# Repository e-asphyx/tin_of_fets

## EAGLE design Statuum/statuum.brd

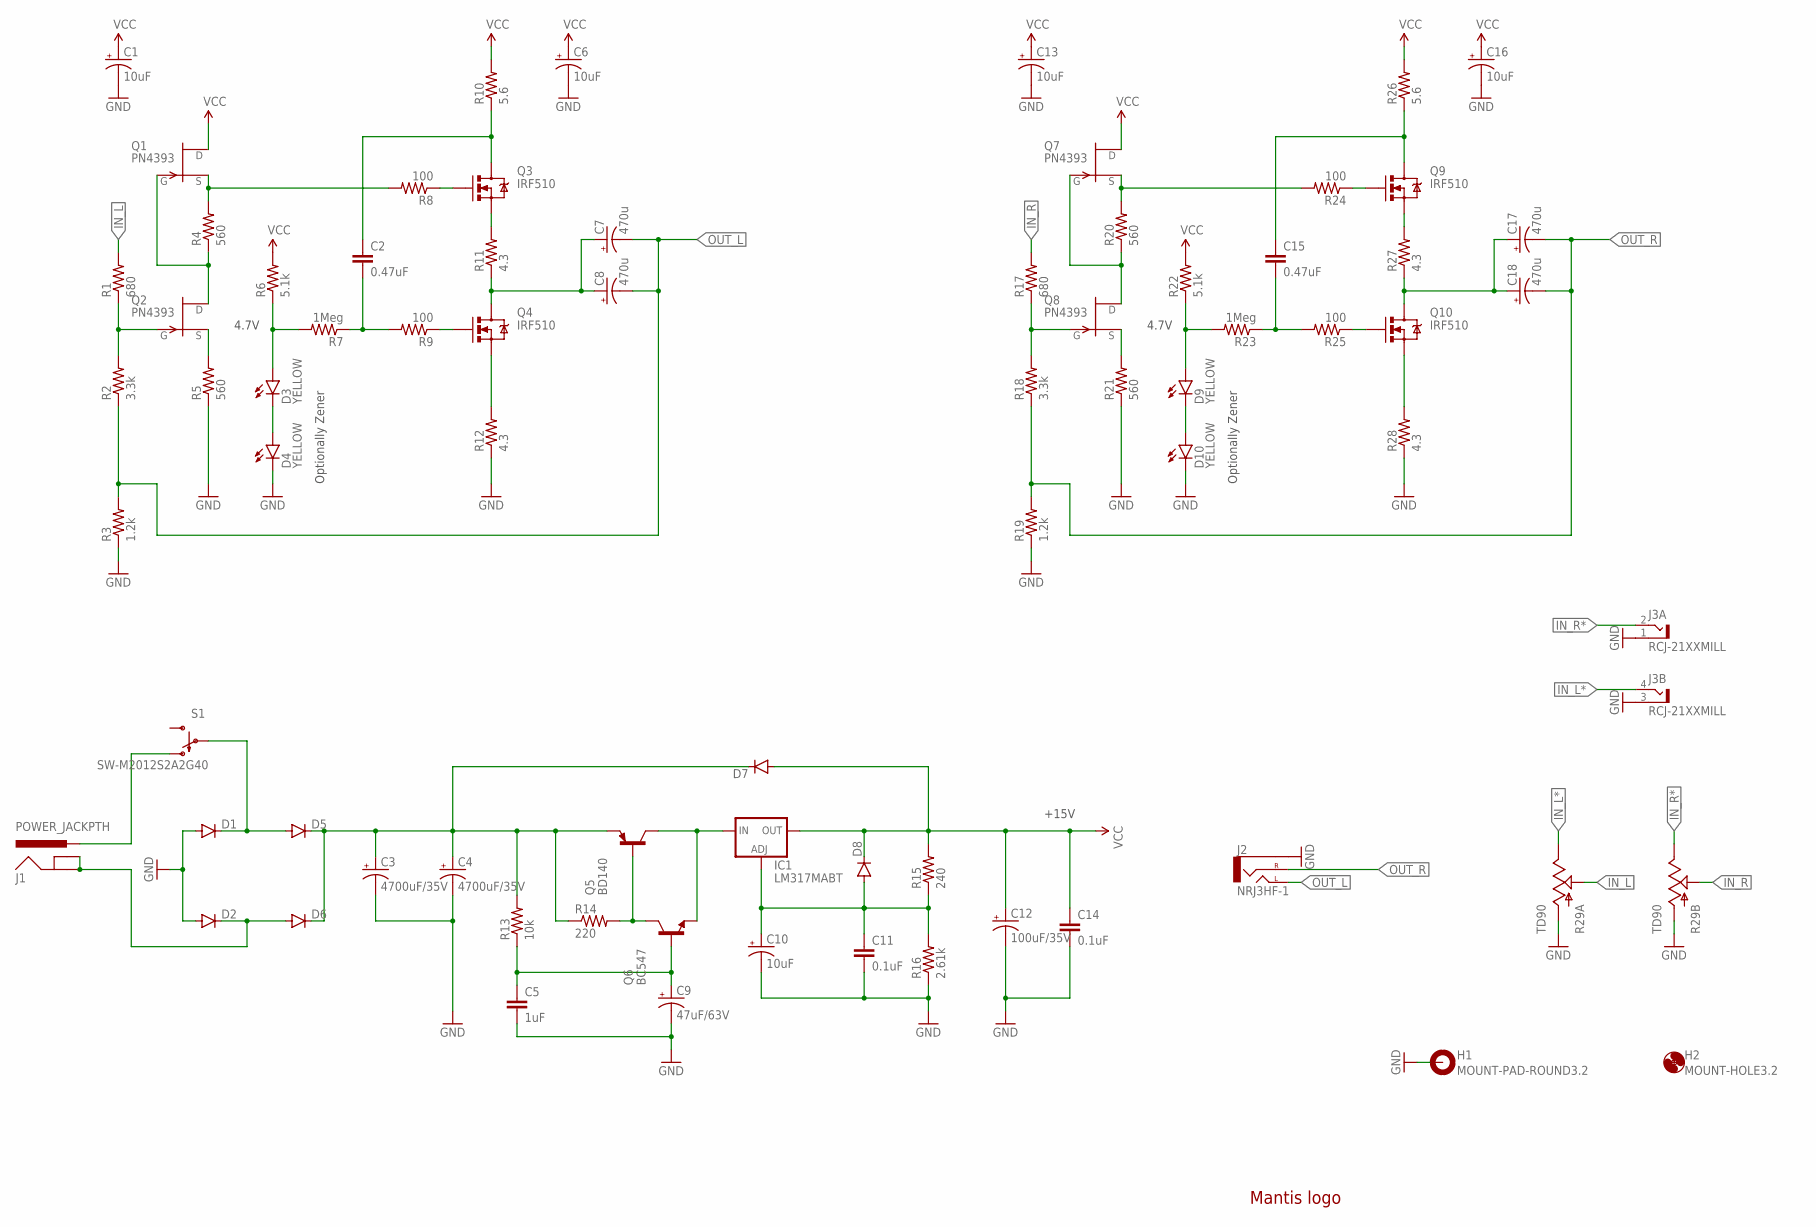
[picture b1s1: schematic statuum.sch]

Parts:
C1, C6, C10, C13, C16: 10uF; CPOL-RADIAL-5/2.5-SM
C2, C15: 0.47uF; C5B3.5
C3, C4: 4700uF/35V; CPOL-RADIAL-16/7.5
C5: 1uF; CAP-PTH-SMALL
C7, C8, C17, C18: 470u; CPOL-RADIAL-8/3.5
C9: 47uF/63V; CPOL-RADIAL-6.5/2.5
C11, C14: 0.1uF; CAP-PTH-SMALL
C12: 100uF/35V; CPOL-RADIAL-8/3.5
D1, D2, D5, D6, D7, D8: DIODEPTH; DIODE-1N4001
D3, D4, D9, D10: YELLOW; LED3MM-SM
H1: MOUNT-PAD-ROUND3.2; 3,2-PAD
H2: MOUNT-HOLE3.2; 3,2
IC1: LM317MABT; TO220L1
J1: POWER_JACKPTH; POWER_JACK_PTH
J2: NRJ3HF-1; NRJ3HF
J3: RCJ-21XXMILL; RCJ-21-MILL
LOGO1: LOGO-MANTIS
Q1, Q2, Q7, Q8: PN4393; TO-92
Q3, Q4, Q9, Q10: IRF510; TO220-HORIZ
Q5: BD140; TO126
Q6: BC547; TO-92
R1, R17: 680; AXIAL-0.4
R2, R18: 3.3k; AXIAL-0.4
R3, R19: 1.2k; AXIAL-0.4
R4, R5, R20, R21: 560; AXIAL-0.4
R6, R22: 5.1k; AXIAL-0.4
R7, R23: 1Meg; AXIAL-0.4
R8, R9, R24, R25: 100; AXIAL-0.4
R10, R26: 5.6; AXIAL-0.4
R11, R12, R27, R28: 4.3; AXIAL-0.4
R13: 10k; AXIAL-0.4
R14: 220; AXIAL-0.4
R15: 240; AXIAL-0.4
R16: 2.61k; AXIAL-0.4
R29: TD90; PTD902
S1: SW-M2012S2A2G40

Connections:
GND: C1.2 (-), C3.2 (-), C4.2 (-), C5.2, C6.2 (-), C9.2 (-), C10.2 (-), C11.2, C12.2 (-), C13.2 (-), C14.2, C16.2 (-), D1.A, D2.A, D4.K (C), D10.K (C), H1.B3,2, J2.S (SLEEVE), J3.1 (S), J3.3 (S), R3.P$1 (1), R5.P$1 (1), R12.P$1 (1), R16.P$1 (1), R19.P$1 (1), R21.P$1 (1), R28.P$1 (1), R29.R1.1 (A), R29.R2.1 (A)
IN_L: R1.P$2 (2), R29.R1.2 (S)
IN_L*: J3.4 (T), R29.R1.3 (E)
IN_R: R17.P$2 (2), R29.R2.2 (S)
IN_R*: J3.2 (T), R29.R2.3 (E)
unnamed: Q1.2 (S), R4.P$2 (2), R8.P$2 (2)
unnamed: Q1.3 (G), Q2.1 (D), R4.P$1 (1)
unnamed: Q2.2 (S), R5.P$2 (2)
unnamed: D3.K (C), D4.A
unnamed: Q3.1 (G), R8.P$1 (1)
unnamed: Q2.3 (G), R1.P$1 (1), R2.P$2 (2)
unnamed: Q3.3 (S), R11.P$2 (2)
unnamed: Q4.1 (G), R9.P$1 (1)
unnamed: Q9.3 (S), R27.P$2 (2)
unnamed: Q4.3 (S), R12.P$2 (2)
unnamed: C2.1, Q3.2 (D), R10.P$1 (1)
unnamed: C7.1 (+), C8.1 (+), Q4.2 (D), R11.P$1 (1)
unnamed: D1.C, D5.A, S1.S
unnamed: D3.A, R6.P$1 (1), R7.P$2 (2)
unnamed: C2.2, R7.P$1 (1), R9.P$2 (2)
unnamed: Q7.2 (S), R20.P$2 (2), R24.P$2 (2)
unnamed: Q7.3 (G), Q8.1 (D), R20.P$1 (1)
unnamed: Q8.2 (S), R21.P$2 (2)
unnamed: Q8.3 (G), R17.P$1 (1), R18.P$2 (2)
unnamed: Q9.1 (G), R24.P$1 (1)
unnamed: Q10.1 (G), R25.P$1 (1)
unnamed: Q10.3 (S), R28.P$2 (2)
unnamed: C15.1, Q9.2 (D), R26.P$1 (1)
unnamed: D9.A, R22.P$1 (1), R23.P$2 (2)
unnamed: D9.K (C), D10.A
unnamed: Q5.3 (B), Q6.1 (C), R14.P$2 (2)
unnamed: C5.1, C9.1 (+), Q6.2 (B), R13.P$1 (1)
unnamed: C15.2, R23.P$1 (1), R25.P$2 (2)
unnamed: C17.1 (+), C18.1 (+), Q10.2 (D), R27.P$1 (1)
unnamed: D2.C, D6.A, J1.GND, J1.GNDBREAK
unnamed: C10.1 (+), C11.1, D8.A, IC1.1 (ADJ), R15.P$1 (1), R16.P$2 (2)
unnamed: C3.1 (+), C4.1 (+), D5.C, D6.C, D7.C, Q5.1 (E), R13.P$2 (2), R14.P$1 (1)
unnamed: J1.PWR, S1.UP-CONNECT (O)
unnamed: IC1.3 (IN), Q5.2 (C), Q6.3 (E)
OUT_L: C7.2 (-), C8.2 (-), J2.T (LEFT), R2.P$1 (1), R3.P$2 (2)
OUT_R: C17.2 (-), C18.2 (-), J2.R (RIGHT), R18.P$1 (1), R19.P$2 (2)
VCC: C1.1 (+), C6.1 (+), C12.1 (+), C13.1 (+), C14.1, C16.1 (+), D7.A, D8.C, IC1.2 (OUT), Q1.1 (D), Q7.1 (D), R6.P$2 (2), R10.P$2 (2), R15.P$2 (2), R22.P$2 (2), R26.P$2 (2)

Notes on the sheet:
Optionally Zener
+15V
4.7V

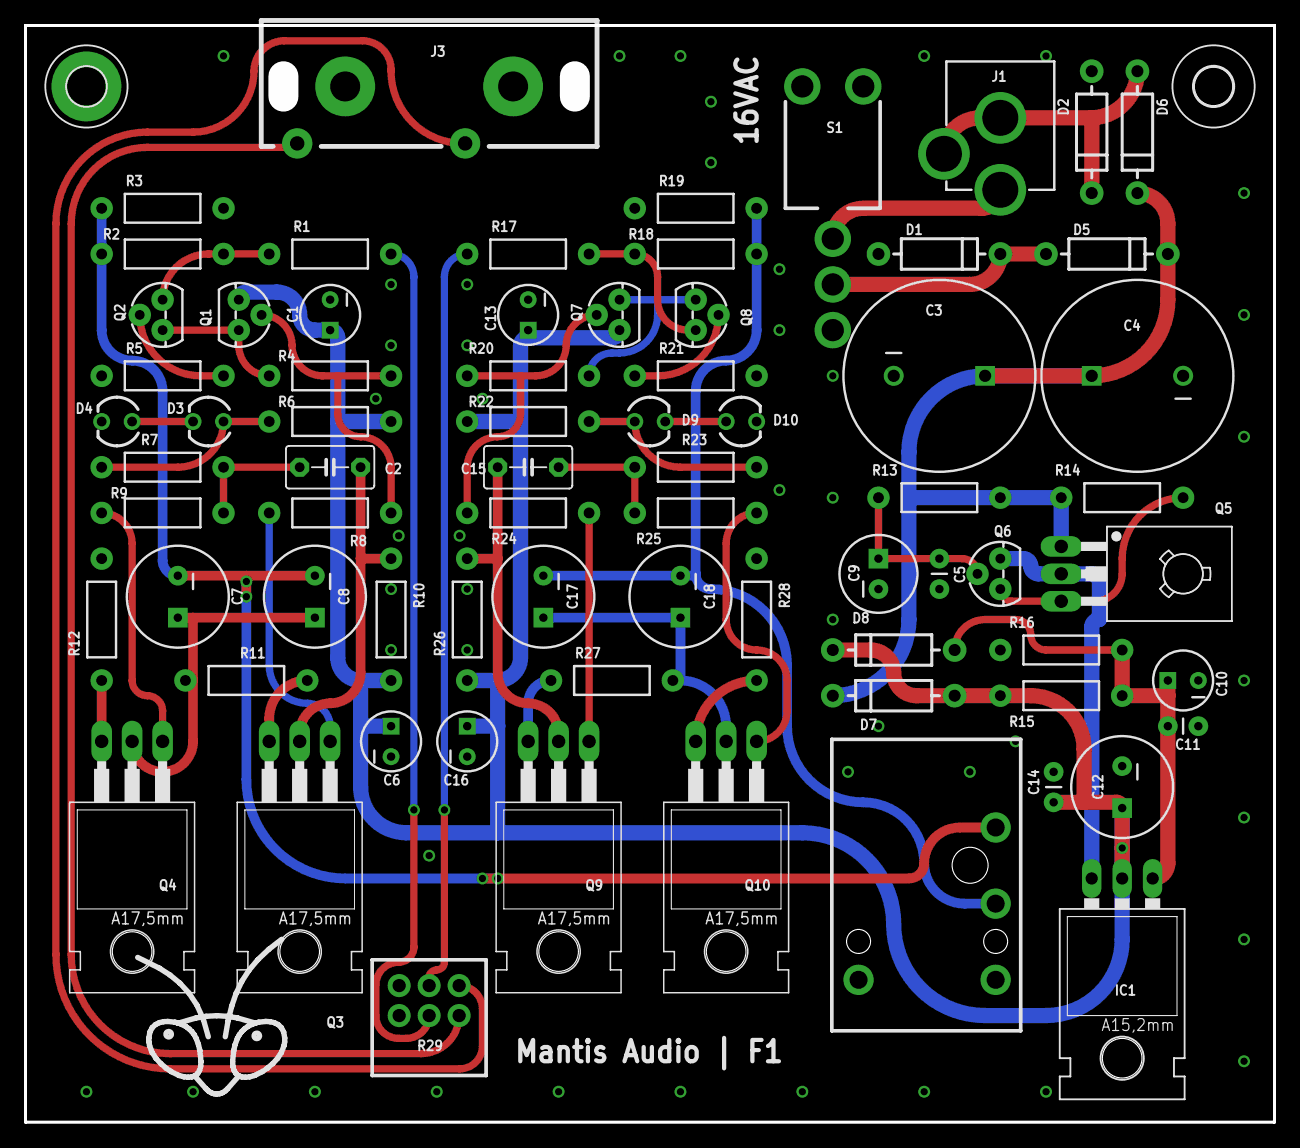
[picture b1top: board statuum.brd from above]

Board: 2 copper layers, 101.9 x 89.2 mm, 75 parts (0 on the bottom side), 42 nets.

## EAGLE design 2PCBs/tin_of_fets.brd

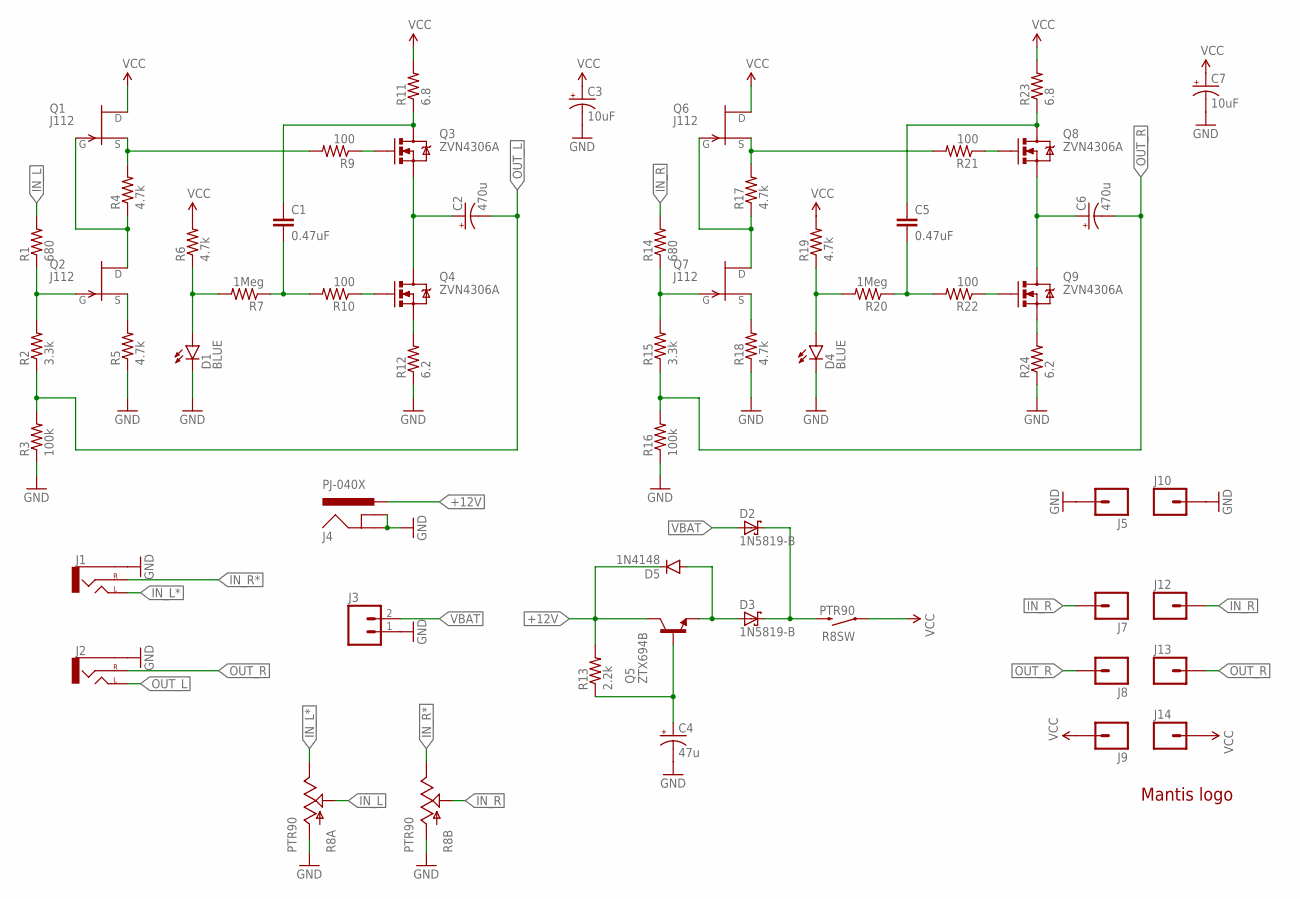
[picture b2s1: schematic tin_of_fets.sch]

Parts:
C1, C5: 0.47uF; C5B3.5
C2, C6: 470u; CPOL-RADIAL-8/3.5
C3, C7: 10uF; CPOL-RADIAL-10UF-25V-SM
C4: 47u; CPOL-RADIAL-10UF-25V-SM
D1, D4: BLUE; LED3MM-SM
D2, D3: 1N5819-B; DO41-7.6
D5: 1N4148; DIODE-1N4148
J1, J2: AUDIO-JACKPTH; AUDIO-JACK
J3: M02PTH; 1X02
J4: PJ-040X
J5, J7, J8, J9, J10, J12, J13, J14: M01PTH; 1X01
LOGO1: LOGO-MANTIS
Q1, Q2, Q6, Q7: J112; TO-92
Q3, Q4, Q8, Q9: ZVN4306A; TO-92
Q5: ZTX694B; TO-92
R1, R14: 680; AXIAL-0.4-SM
R2, R15: 3.3k; AXIAL-0.4-SM
R3, R16: 100k; AXIAL-0.4-SM
R4, R5, R6, R17, R18, R19: 4.7k; AXIAL-0.4-SM
R7, R20: 1Meg; AXIAL-0.4-SM
R8: PTR90; PTR902
R9, R10, R21, R22: 100; AXIAL-0.4-SM
R11, R23: 6.8; AXIAL-0.4-SM
R12, R24: 6.2; AXIAL-0.4-SM
R13: 2.2k; AXIAL-0.4-SM

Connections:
+12V: D5.C, J4.1 (PWR), Q5.3 (C), R13.P$2 (2)
GND: C3.2 (-), C4.2 (-), C7.2 (-), D1.K (C), D4.K (C), J1.SLEEVE, J2.SLEEVE, J3.1, J4.2 (GND), J4.3 (GNDBREAK), J5.1, J10.1, R3.P$1 (1), R5.P$1 (1), R8.R1.1 (A), R8.R2.1 (A), R12.P$1 (1), R16.P$1 (1), R18.P$1 (1), R24.P$1 (1)
IN_L: R1.P$2 (2), R8.R1.2 (S)
IN_L*: J1.TIP (LEFT), R8.R1.3 (E)
IN_R: J7.1, J12.1, R8.R2.2 (S), R14.P$2 (2)
IN_R*: J1.RING (RIGHT), R8.R2.3 (E)
unnamed: Q1.2 (S), R4.P$2 (2), R9.P$2 (2)
unnamed: Q1.3 (G), Q2.1 (D), R4.P$1 (1)
unnamed: Q2.2 (S), R5.P$2 (2)
unnamed: Q6.2 (S), R17.P$2 (2), R21.P$2 (2)
unnamed: Q3.2 (G), R9.P$1 (1)
unnamed: Q2.3 (G), R1.P$1 (1), R2.P$2 (2)
unnamed: Q6.3 (G), Q7.1 (D), R17.P$1 (1)
unnamed: Q4.2 (G), R10.P$1 (1)
unnamed: Q4.1 (S), R12.P$2 (2)
unnamed: C1.1, Q3.3 (D), R11.P$1 (1)
unnamed: Q7.2 (S), R18.P$2 (2)
unnamed: C1.2, R7.P$1 (1), R10.P$2 (2)
unnamed: D1.A, R6.P$1 (1), R7.P$2 (2)
unnamed: Q7.3 (G), R14.P$1 (1), R15.P$2 (2)
unnamed: Q8.2 (G), R21.P$1 (1)
unnamed: Q9.2 (G), R22.P$1 (1)
unnamed: Q9.1 (S), R24.P$2 (2)
unnamed: C5.1, Q8.3 (D), R23.P$1 (1)
unnamed: C5.2, R20.P$1 (1), R22.P$2 (2)
unnamed: D4.A, R19.P$1 (1), R20.P$2 (2)
unnamed: D3.A, D5.A, Q5.1 (E)
unnamed: C4.1 (+), Q5.2 (B), R13.P$1 (1)
OUT_L: C2.2 (-), J2.TIP (LEFT), R2.P$1 (1), R3.P$2 (2)
OUT_L*: C2.1 (+), Q3.1 (S), Q4.3 (D)
OUT_R: C6.2 (-), J2.RING (RIGHT), J8.1, J13.1, R15.P$1 (1), R16.P$2 (2)
OUT_R*: C6.1 (+), Q8.1 (S), Q9.3 (D)
VBAT: D2.A, J3.2
VCC: C3.1 (+), C7.1 (+), J9.1, J14.1, Q1.1 (D), Q6.1 (D), R6.P$2 (2), R8.SW1 (1), R11.P$2 (2), R19.P$2 (2), R23.P$2 (2)
VCC*: D2.C, D3.C, R8.SW2 (2)

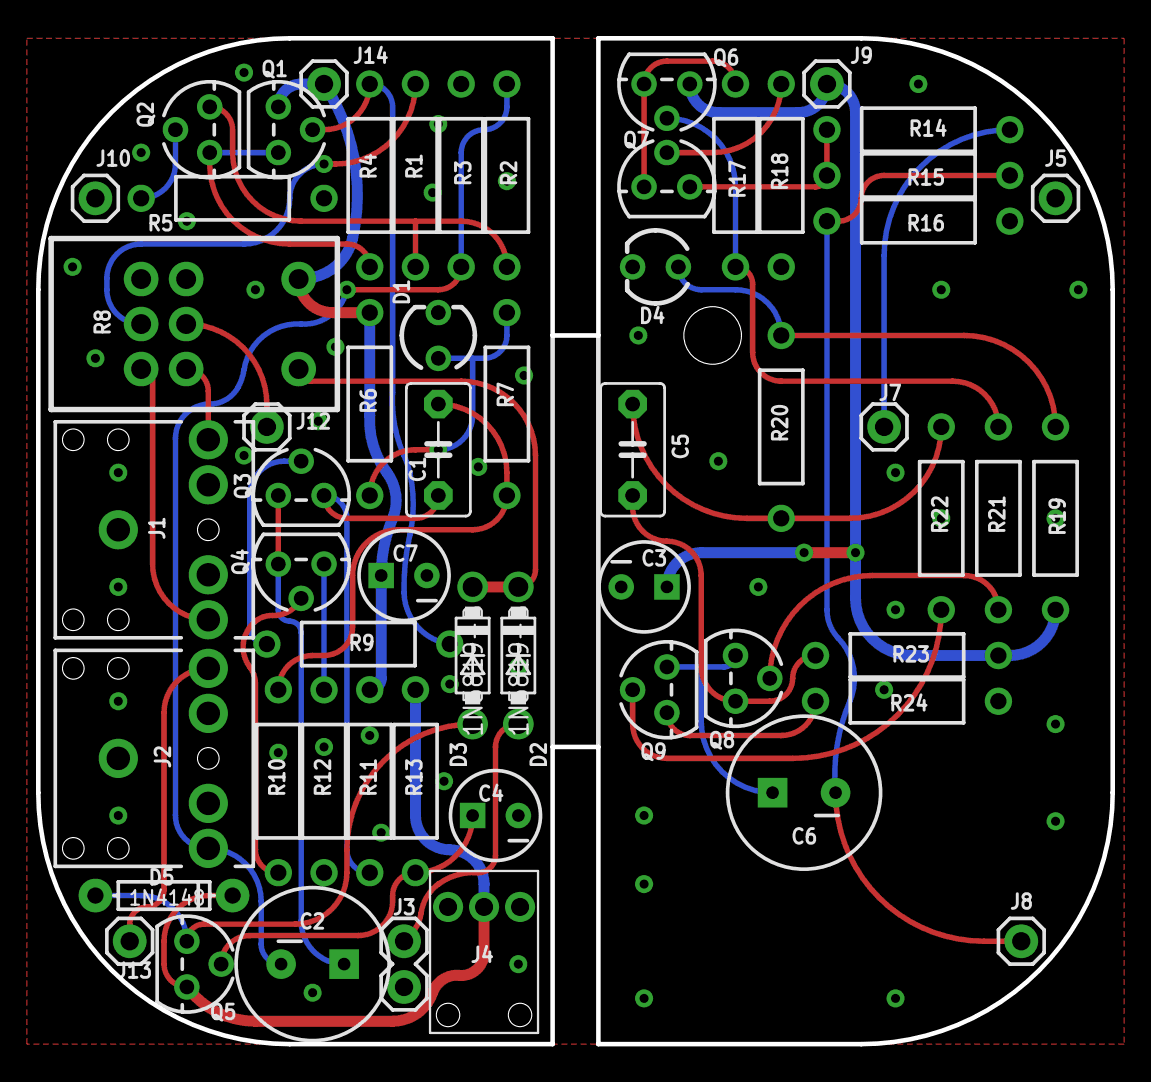
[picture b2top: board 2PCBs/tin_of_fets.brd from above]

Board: 2 copper layers, 59.7 x 55.9 mm, 58 parts (1 on the bottom side), 35 nets.

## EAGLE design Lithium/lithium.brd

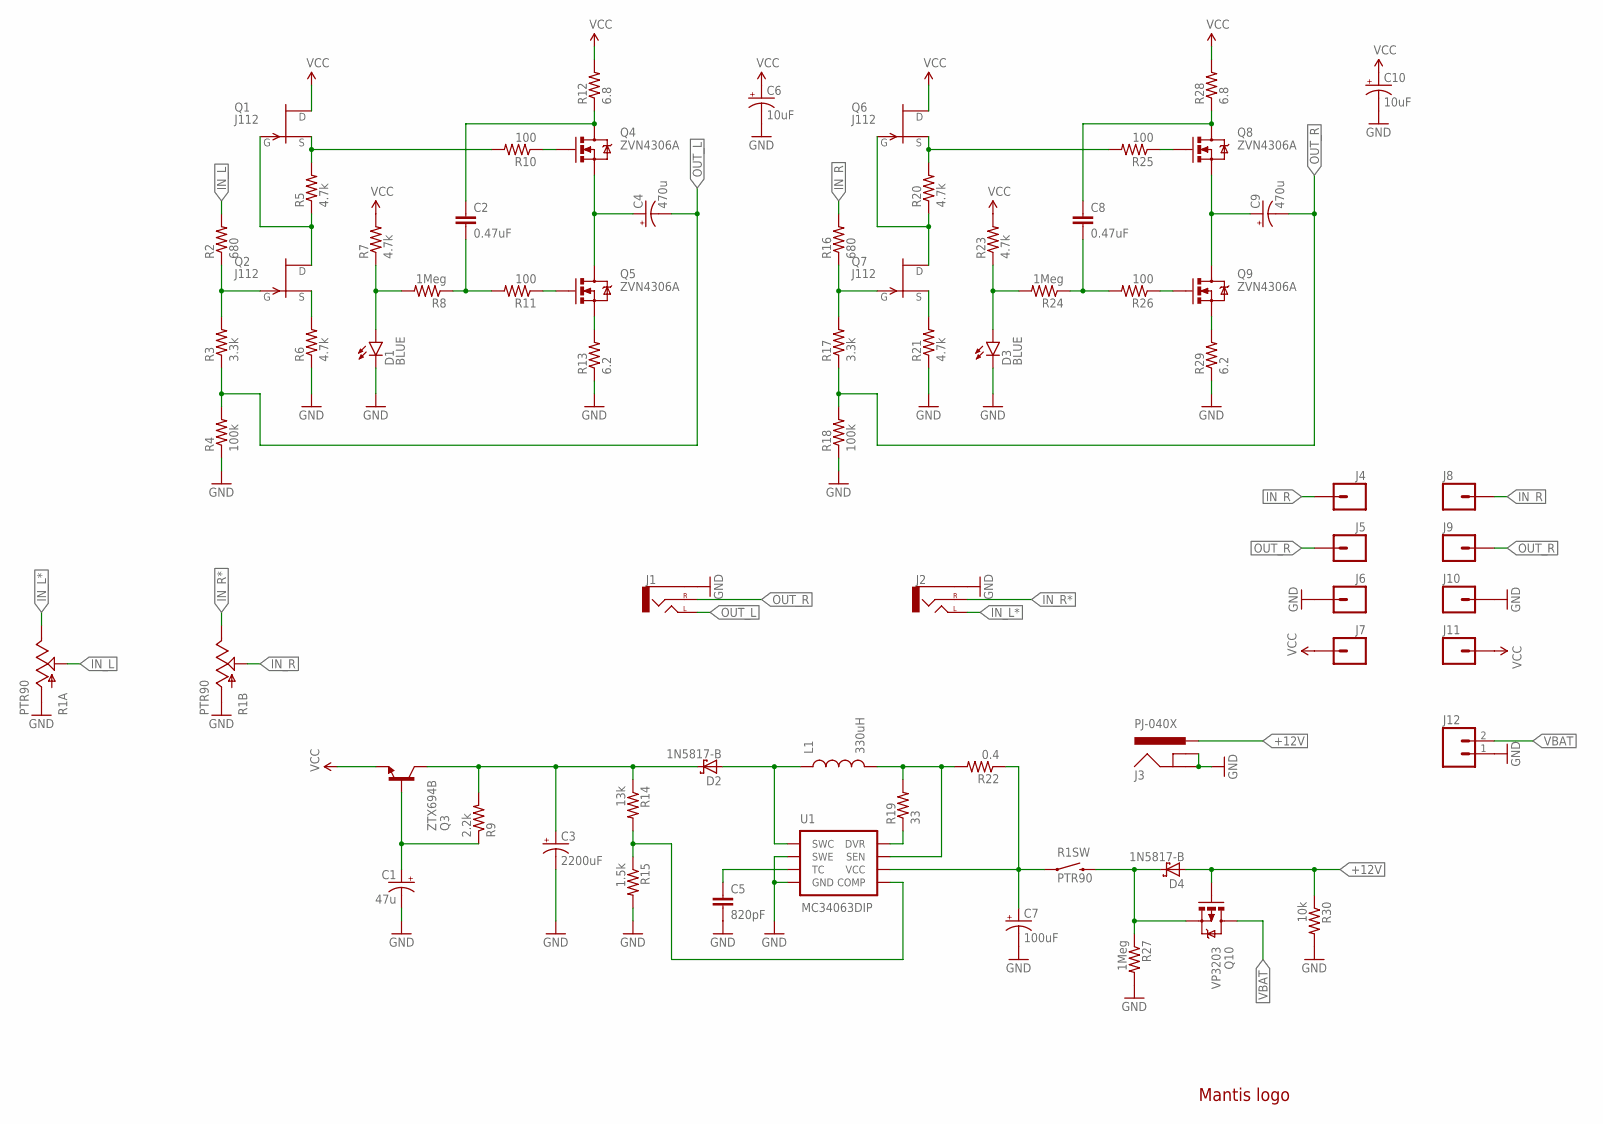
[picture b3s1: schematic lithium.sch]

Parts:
C1: 47u; CPOL-RADIAL-10UF-25V-SM
C2, C8: 0.47uF; C5B3.5
C3: 2200uF; CPOL-RADIAL-1000UF-25V
C4, C9: 470u; CPOL-RADIAL-8/3.5
C5: 820pF; CAP-PTH-SMALL
C6, C10: 10uF; CPOL-RADIAL-10UF-25V-SM
C7: 100uF; CPOL-RADIAL-100UF-25V
D1, D3: BLUE; LED3MM-SM
D2, D4: 1N5817-B; DO41-7.6
J1, J2: AUDIO-JACKPTH; AUDIO-JACK
J3: PJ-040X
J4, J5, J6, J7, J8, J9, J10, J11: M01PTH; 1X01
J12: M02PTH; 1X02
L1: 330uH; RLB0912
LOGO1: LOGO-MANTIS
Q1, Q2, Q6, Q7: J112; TO-92
Q3: ZTX694B; TO-92
Q4, Q5, Q8, Q9: ZVN4306A; TO-92
Q10: VP3203; TO-92
R1: PTR90; PTR902
R2, R16: 680; AXIAL-0.4-SM
R3, R17: 3.3k; AXIAL-0.4-SM
R4, R18: 100k; AXIAL-0.4-SM
R5, R6, R7, R20, R21, R23: 4.7k; AXIAL-0.4-SM
R8, R24, R27: 1Meg; AXIAL-0.4-SM
R9: 2.2k; AXIAL-0.4-SM
R10, R11, R25, R26: 100; AXIAL-0.4-SM
R12, R28: 6.8; AXIAL-0.4-SM
R13, R29: 6.2; AXIAL-0.4-SM
R14: 13k; AXIAL-0.4-SM
R15: 1.5k; AXIAL-0.4-SM
R19: 33; AXIAL-0.4-SM
R22: 0.4; AXIAL-0.4-SM
R30: 10k; AXIAL-0.4-SM
U1: MC34063DIP; DIP-08

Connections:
+12V: D4.A, J3.1 (PWR), Q10.2 (G), R30.P$1 (1)
GND: C1.2 (-), C3.-, C5.2, C6.2 (-), C7.2 (-), C10.2 (-), D1.K (C), D3.K (C), J1.SLEEVE, J2.SLEEVE, J3.2 (GND), J3.3 (GNDBREAK), J6.1, J10.1, J12.1, R1.R1.1 (A), R1.R2.1 (A), R4.P$1 (1), R6.P$1 (1), R13.P$1 (1), R15.P$2 (2), R18.P$1 (1), R21.P$1 (1), R27.P$2 (2), R29.P$1 (1), R30.P$2 (2), U1.2 (SWE), U1.4 (GND)
IN_L: R1.R1.2 (S), R2.P$2 (2)
IN_L*: J2.TIP (LEFT), R1.R1.3 (E)
IN_R: J4.1, J8.1, R1.R2.2 (S), R16.P$2 (2)
IN_R*: J2.RING (RIGHT), R1.R2.3 (E)
unnamed: Q1.2 (S), R5.P$2 (2), R10.P$2 (2)
unnamed: Q1.3 (G), Q2.1 (D), R5.P$1 (1)
unnamed: Q2.2 (S), R6.P$2 (2)
unnamed: Q6.2 (S), R20.P$2 (2), R25.P$2 (2)
unnamed: Q4.2 (G), R10.P$1 (1)
unnamed: Q2.3 (G), R2.P$1 (1), R3.P$2 (2)
unnamed: Q6.3 (G), Q7.1 (D), R20.P$1 (1)
unnamed: Q5.2 (G), R11.P$1 (1)
unnamed: C5.1, U1.3 (TC)
unnamed: Q5.1 (S), R13.P$2 (2)
unnamed: C2.1, Q4.3 (D), R12.P$1 (1)
unnamed: Q7.2 (S), R21.P$2 (2)
unnamed: C2.2, R8.P$1 (1), R11.P$2 (2)
unnamed: D1.A, R7.P$1 (1), R8.P$2 (2)
unnamed: Q7.3 (G), R16.P$1 (1), R17.P$2 (2)
unnamed: Q8.2 (G), R25.P$1 (1)
unnamed: Q9.2 (G), R26.P$1 (1)
unnamed: R19.P$1 (1), U1.8 (DVR)
unnamed: Q9.1 (S), R29.P$2 (2)
unnamed: C8.1, Q8.3 (D), R28.P$1 (1)
unnamed: C8.2, R24.P$1 (1), R26.P$2 (2)
unnamed: D3.A, R23.P$1 (1), R24.P$2 (2)
unnamed: C7.1 (+), R1.SW1 (1), R22.P$1 (1), U1.6 (VCC)
unnamed: C1.1 (+), Q3.2 (B), R9.P$1 (1)
unnamed: D2.A, L1.1, U1.1 (SWC)
unnamed: L1.2, R19.P$2 (2), R22.P$2 (2), U1.7 (SEN)
unnamed: R14.P$2 (2), R15.P$1 (1), U1.5 (COMP)
unnamed: D4.C, Q10.1 (S), R1.SW2 (2), R27.P$1 (1)
OUT_L: C4.2 (-), J1.TIP (LEFT), R3.P$1 (1), R4.P$2 (2)
OUT_L*: C4.1 (+), Q4.1 (S), Q5.3 (D)
OUT_R: C9.2 (-), J1.RING (RIGHT), J5.1, J9.1, R17.P$1 (1), R18.P$2 (2)
OUT_R*: C9.1 (+), Q8.1 (S), Q9.3 (D)
VBAT: J12.2, Q10.3 (D)
VCC: C6.1 (+), C10.1 (+), J7.1, J11.1, Q1.1 (D), Q3.1 (E), Q6.1 (D), R7.P$2 (2), R12.P$2 (2), R23.P$2 (2), R28.P$2 (2)
VSMPS: C3.+, D2.C, Q3.3 (C), R9.P$2 (2), R14.P$1 (1)

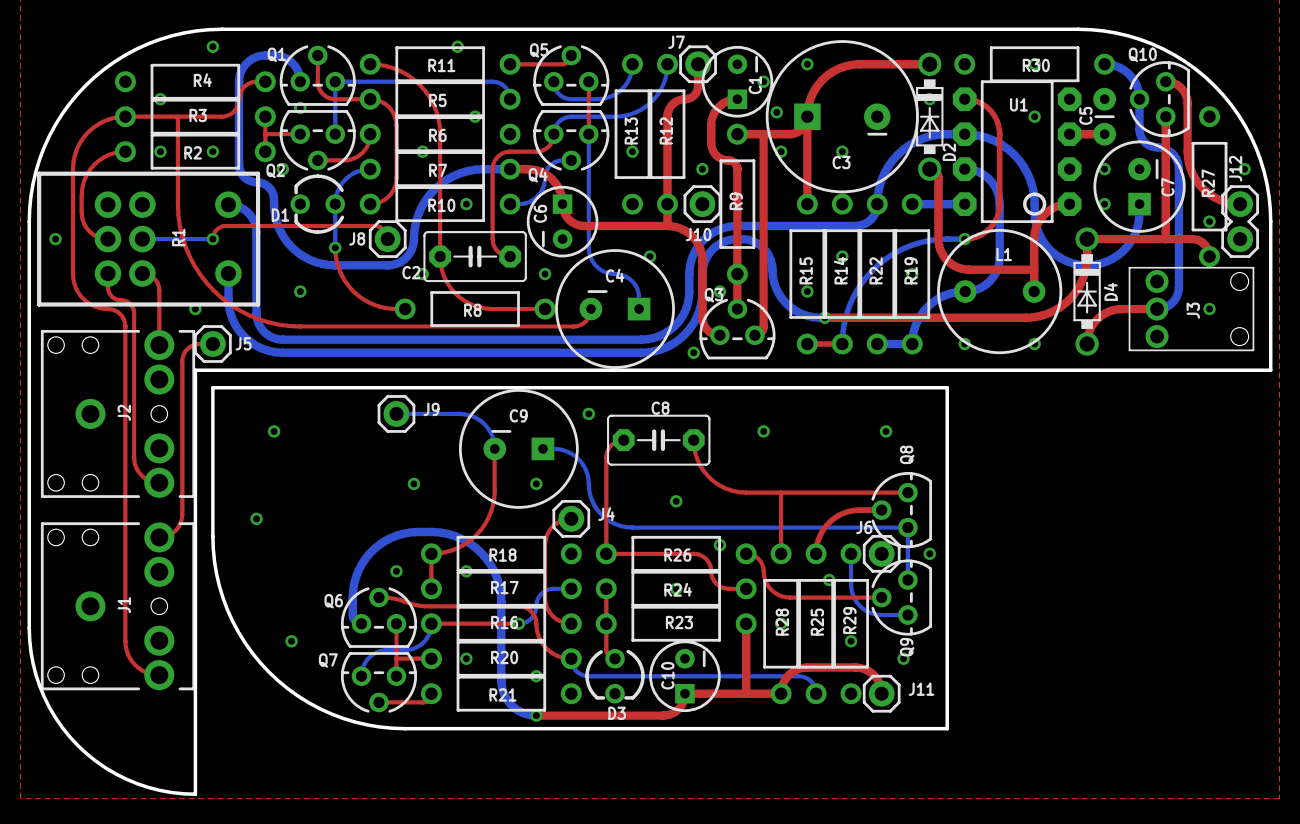
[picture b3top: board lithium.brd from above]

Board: 2 copper layers, 90.2 x 55.6 mm, 69 parts (1 on the bottom side), 41 nets.

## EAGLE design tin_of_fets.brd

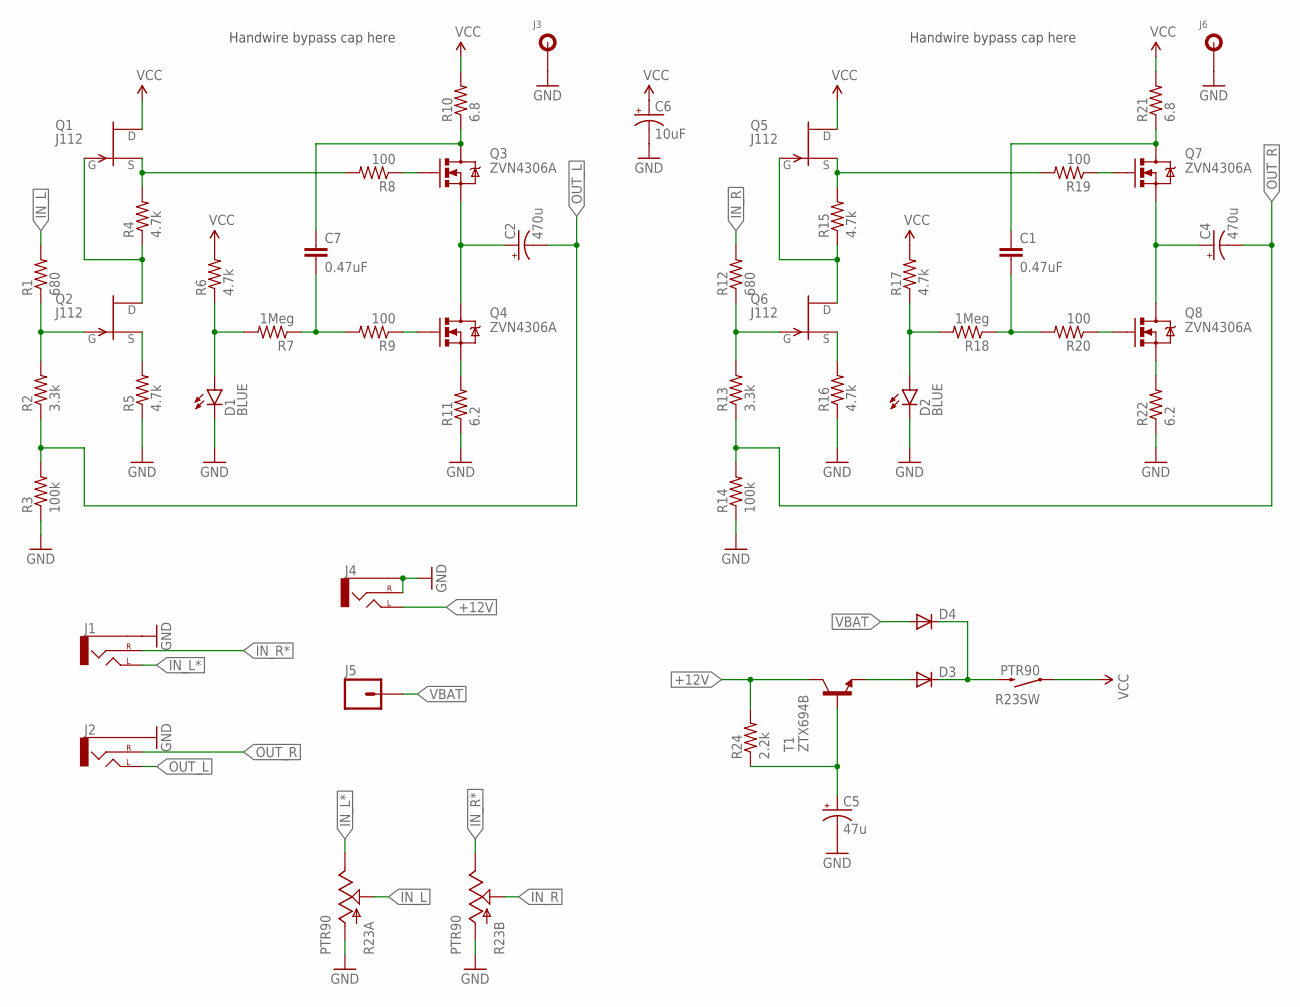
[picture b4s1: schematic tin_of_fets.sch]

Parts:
A1, A2: 9V-BATTERY-DOCU; 9V-BATTERY-DIM
A3: ALTOIDS-DOCU; ALTOIDS-INNER-DIM
C1, C7: 0.47uF; C5B3.5
C2, C4: 470u; CPOL-RADIAL-1000UF-25V
C5: 47u; CPOL-RADIAL-10UF-25V
C6: 10uF; CPOL-RADIAL-10UF-25V
D1, D2: BLUE; LED3MM
D3, D4: DIODE-C1702-05; C1702-05
J1, J2, J4: AUDIO-JACK2.5MM; STEREOJACK2.5MM_STEREOJACK2.5MM
J3, J6: PAD-NO-THERMAL
J5: M01PTH; 1X01
Q1, Q2, Q5, Q6: J112; TO92
Q3, Q4, Q7, Q8: ZVN4306A; TO-92
R1, R12: 680; AXIAL-0.1-SM
R2, R13: 3.3k; AXIAL-0.1-SM
R3, R14: 100k; AXIAL-0.1-SM
R4, R5, R6, R15, R16, R17: 4.7k; AXIAL-0.1-SM
R7, R18: 1Meg; AXIAL-0.1-SM
R8, R9, R19, R20: 100; AXIAL-0.1-SM
R10, R21: 6.8; AXIAL-0.1-SM
R11, R22: 6.2; AXIAL-0.1-SM
R23: PTR90; PTR902
R24: 2.2k; AXIAL-0.1-SM
T1: ZTX694B; TO92

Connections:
+12V: J4.TIP1 (LEFT), J4.TIP2 (LEFT), R24.P$2 (2), T1.1 (C)
GND: C5.2 (-), C6.2 (-), D1.K (C), D2.K (C), J1.SHIELD (SLEEVE), J2.SHIELD (SLEEVE), J3.P$1, J4.RING (RIGHT), J4.SHIELD (SLEEVE), J6.P$1, R3.P$1 (1), R5.P$1 (1), R11.P$1 (1), R14.P$1 (1), R16.P$1 (1), R22.P$1 (1), R23.R1.1 (A), R23.R2.1 (A)
IN_L: R1.P$2 (2), R23.R1.2 (S)
IN_L*: J1.TIP1 (LEFT), J1.TIP2 (LEFT), R23.R1.3 (E)
IN_R: R12.P$2 (2), R23.R2.2 (S)
IN_R*: J1.RING (RIGHT), R23.R2.3 (E)
unnamed: Q1.2 (S), R4.P$2 (2), R8.P$2 (2)
unnamed: Q1.1 (G), Q2.3 (D), R4.P$1 (1)
unnamed: Q2.2 (S), R5.P$2 (2)
unnamed: Q5.2 (S), R15.P$2 (2), R19.P$2 (2)
unnamed: Q3.2 (G), R8.P$1 (1)
unnamed: Q2.1 (G), R1.P$1 (1), R2.P$2 (2)
unnamed: Q5.1 (G), Q6.3 (D), R15.P$1 (1)
unnamed: Q4.2 (G), R9.P$1 (1)
unnamed: Q4.1 (S), R11.P$2 (2)
unnamed: C7.1, Q3.3 (D), R10.P$1 (1)
unnamed: Q6.2 (S), R16.P$2 (2)
unnamed: C7.2, R7.P$1 (1), R9.P$2 (2)
unnamed: D1.A, R6.P$1 (1), R7.P$2 (2)
unnamed: Q6.1 (G), R12.P$1 (1), R13.P$2 (2)
unnamed: Q7.2 (G), R19.P$1 (1)
unnamed: Q8.2 (G), R20.P$1 (1)
unnamed: Q8.1 (S), R22.P$2 (2)
unnamed: C1.1, Q7.3 (D), R21.P$1 (1)
unnamed: C1.2, R18.P$1 (1), R20.P$2 (2)
unnamed: D2.A, R17.P$1 (1), R18.P$2 (2)
unnamed: D3.A, T1.3 (E)
unnamed: C5.1 (+), R24.P$1 (1), T1.2 (B)
OUT_L: C2.-, J2.TIP1 (LEFT), J2.TIP2 (LEFT), R2.P$1 (1), R3.P$2 (2)
OUT_L*: C2.+, Q3.1 (S), Q4.3 (D)
OUT_R: C4.-, J2.RING (RIGHT), R13.P$1 (1), R14.P$2 (2)
OUT_R*: C4.+, Q7.1 (S), Q8.3 (D)
VBAT: D4.A, J5.1
VCC: C6.1 (+), Q1.3 (D), Q5.3 (D), R6.P$2 (2), R10.P$2 (2), R17.P$2 (2), R21.P$2 (2), R23.SW1 (1)
VCC*: D3.C, D4.C, R23.SW2 (2)

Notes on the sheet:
Handwire bypass cap here

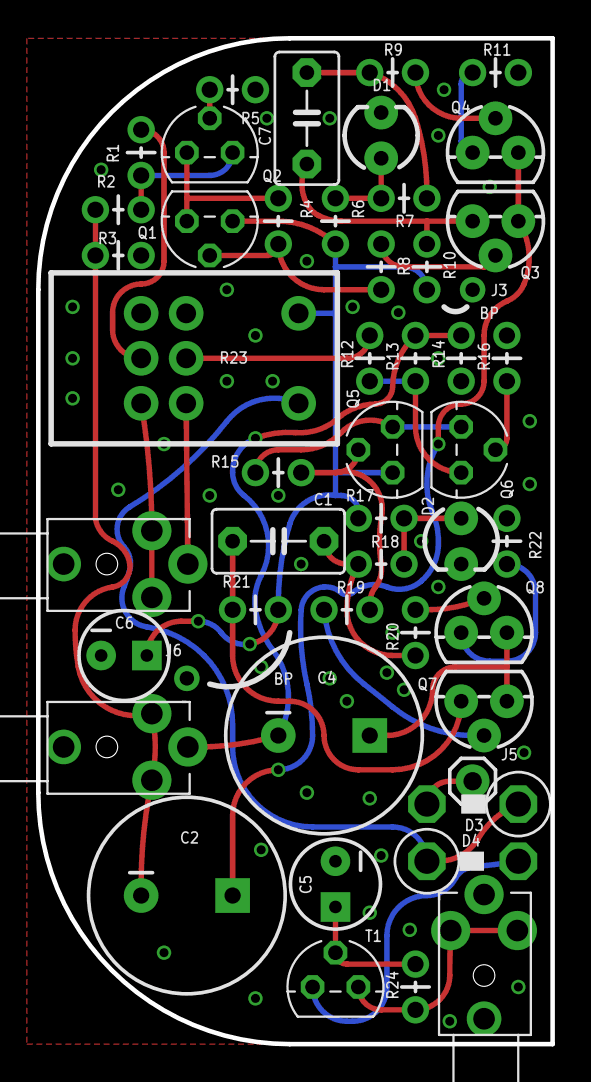
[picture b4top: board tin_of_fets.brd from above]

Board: 2 copper layers, 28.6 x 55.9 mm, 52 parts (0 on the bottom side), 35 nets.

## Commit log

2016-10-14 Initial
2016-10-15 Single bypass cap. No more room
2016-10-15 Added pads for hand-wiring bypass caps
2016-10-15 PDFs
2016-10-15 Followers FB caps changed to .47u film
2016-10-16 Jacks pinout fixed
2016-10-16 Jacks pinout fixed again
2016-10-16 Small fix
2016-10-17 2 PCBs version
2016-10-21 Li-ion powered version WIP
2016-10-21 Stamp holes removed
2016-10-22 Small improvements
2016-10-27 Desktop version of the same design
2016-11-04 Desktop version changed to IRF510 output
2016-11-06 Mounting holes
2016-11-20 VBE multiplier added

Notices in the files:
parts and their libraries:
SparkFun-Connectors: Licensing: Creative Commons ShareAlike 4.0 International - https://creativecommons.org/licenses/by-sa/4.0
